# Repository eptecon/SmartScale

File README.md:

SmartScale: Connected Scale for weight measurement
======

WiFi connected scale.

### Hardware

ESP32 Microcontroller, sparkfun's [OpenScale](https://www.sparkfun.com/products/13261).

### Firmware

The firmware consists of RTOS and applications for measuring and analysing of weight data from sparkfun's [OpenScale](https://www.sparkfun.com/products/13261). 
The data from the scale is sent over UART to ESP32. ESP32 is also able to configure the scale. It connects to a cloud service and provides weight data over MQTT.

## Software

Immediately after connecting with a server over WLAN, the device starts to send the measured weights to the cloud service ([GlueLogics](https://github.com/eptecon/gluelogics)) enabling analytics for your working environment, even without invasive notifications.

---

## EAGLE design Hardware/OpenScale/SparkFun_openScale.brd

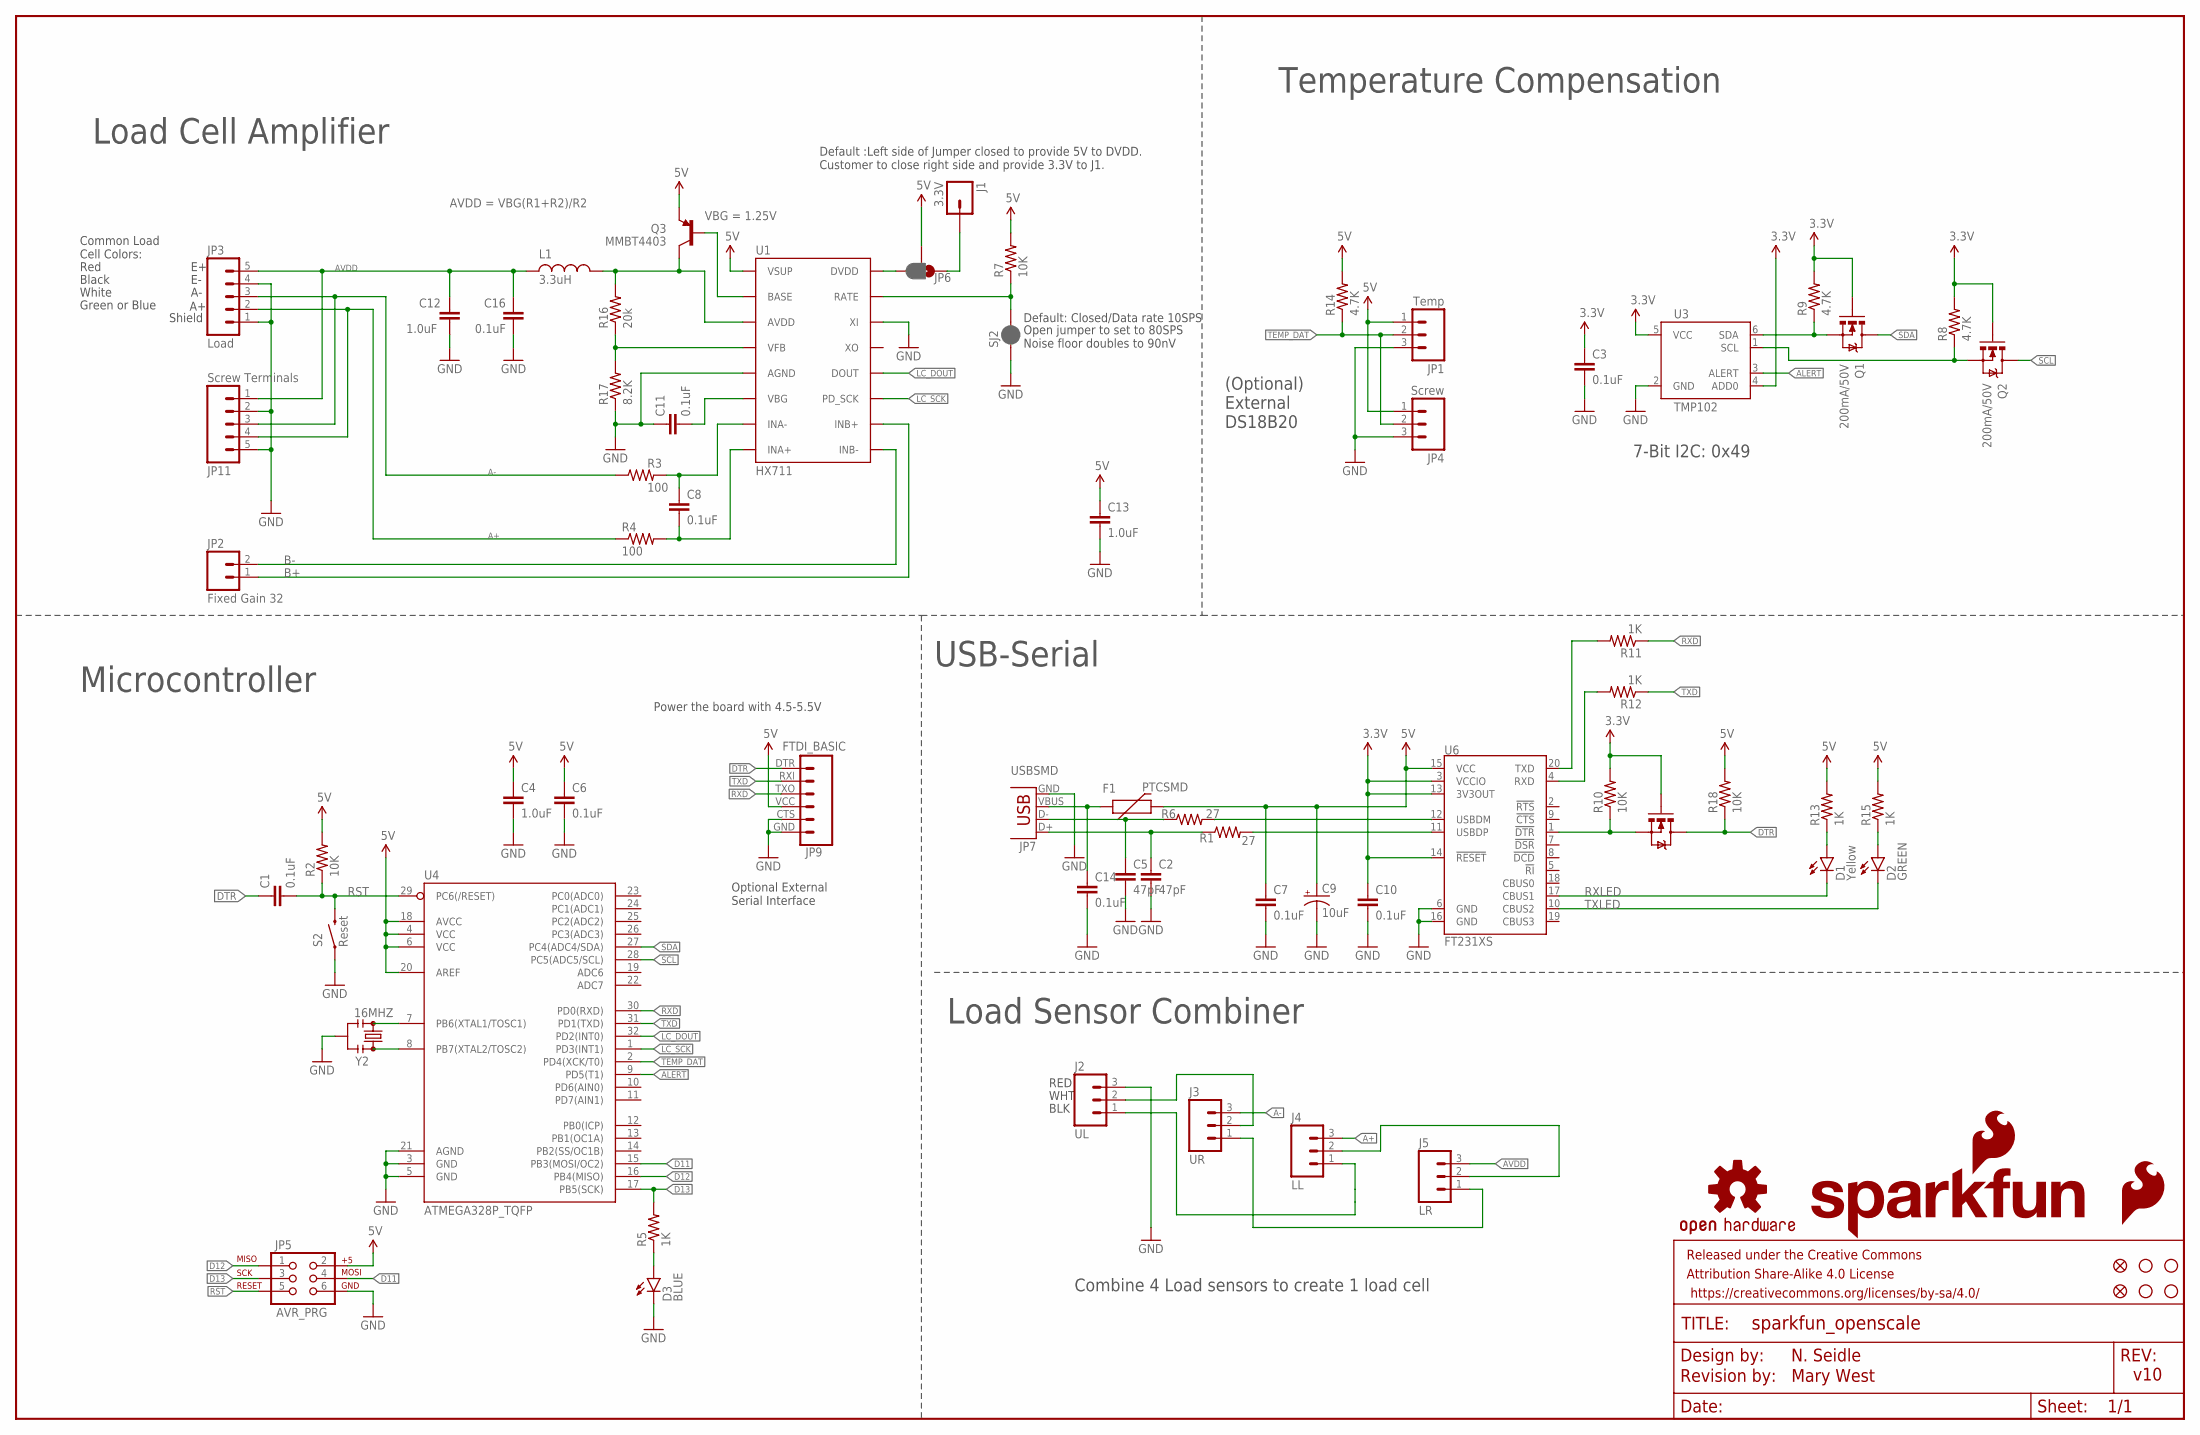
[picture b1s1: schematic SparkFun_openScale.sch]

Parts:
C1, C3, C6, C7, C8, C10, C11, C14, C16: 0.1uF; 0603-CAP
C2, C5: 47pF; 0603-CAP
C4, C12, C13: 1.0uF; 0603-CAP
C9: 10uF; EIA3216
D1: Yellow; LED-1206
D2: GREEN; LED-1206
D3: BLUE; LED-1206
F1: PTCSMD; PTC-1206
FID1, FID2: FIDUCIALUFIDUCIAL; MICRO-FIDUCIAL
FRAME1: FRAME-LEDGER; CREATIVE_COMMONS
J1: 3.3V; 1X01
J2: UL; 1X03
J3: UR; 1X03
J4: LL; 1X03
J5: LR; 1X03
JP1: Temp; 1X03_NO_SILK
JP2: Fixed Gain 32; 1X02
JP3: Load; 1X05_NO_SILK
JP4: Screw; SCREWTERMINAL-3.5MM-3_LOCK.007S
JP5: AVR_PRG; 2X3
JP6: JUMPER-PAD-3-2OF3_NC_BY_PASTE; PAD-JUMPER-3-2OF3_NC_BY_PASTE_YES_SILK_FULL_BOX
JP7: USBSMD; USB-MINIB
JP9: FTDI_BASIC
JP11: Screw Terminals; SCREWTERMINAL-3.5MM-5
L1: 3.3uH; 0805
LOGO2: OSHW-LOGOS; OSHW-LOGO-S
LOGO3: SFE_LOGO_FLAME.1_INCH; SFE_LOGO_FLAME_.1
LOGO4: SFE_LOGO_NAME_FLAME.1_INCH; SFE_LOGO_NAME_FLAME_.1
Q1, Q2: 200mA/50V; SOT23-3
Q3: MMBT4403; SOT23-3
Q4: MOSFET-NCHANNEL2N7002PW; SOT323
R1, R6: 27; 0603
R2, R7, R10, R18: 10K; 0603-RES
R3, R4: 100; 0603-RES
R5, R11, R12, R13, R15: 1K; 0603-RES
R8, R9, R14: 4.7K; 0603-RES
R16: 20k; 0603-RES
R17: 8.2K; 0603-RES
S2: Reset; TACTILE-SWITCH-SMD
SJ2: JUMPER-PAD-2-NC_BY_PASTE; PAD-JUMPER-2-NC_BY_PASTE_YES_SILK
STANDOFF1, STANDOFF2, STANDOFF3, STANDOFF4: STAND-OFF
U1: HX711; SO16
U3: TMP102; SOT563
U4: ATMEGA328P_TQFP; TQFP32-08
U6: FT231XS; SSOP20_L
Y2: 16MHZ; RESONATOR-SMD

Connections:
2: J4.2, J5.2
3.3V: C3.1, C10.1, Q1.1 (G), Q2.1 (G), Q4.1 (G), R8.2, R9.2, R10.2, U3.4 (ADD0), U3.5 (VCC), U6.3 (VCCIO), U6.13 (3V3OUT), U6.14 (!RESET)
5V: C4.1, C6.1, C7.1, C9.A (+), C13.1, F1.2, JP1.1, JP4.1, JP5.2, JP6.2, JP9.VCC (4), Q3.2 (E), R2.2, R7.2, R13.2, R14.2, R15.2, R18.2, U1.1 (VSUP), U4.4 (VCC), U4.6 (VCC), U4.18 (AVCC), U4.20 (AREF), U6.15 (VCC)
A+: J4.3, JP3.2, JP11.4, R4.1
A-: J3.3, JP3.3, JP11.3, R3.1
ALERT: U3.3 (ALERT), U4.9 (PD5(T1))
AVDD: C12.2, C16.1, J5.3, JP3.5, JP11.1, L1.1
B+: JP2.1, U1.10 (INB+)
B-: JP2.2, U1.9 (INB-)
D11: JP5.4, U4.15 (PB3(MOSI/OC2))
D12: JP5.1, U4.16 (PB4(MISO))
D13: JP5.3, R5.2, U4.17 (PB5(SCK))
DTR: C1.1, JP9.DTR (1), Q4.3 (D), R18.1
GND: C2.2, C3.2, C4.2, C5.2, C6.2, C7.2, C9.C (-), C10.2, C11.1, C12.1, C13.2, C14.2, C16.2, D3.C, J2.3, JP1.3, JP3.1, JP3.4, JP4.3, JP5.6, JP7.GND, JP9.CTS (5), JP9.GND (6), JP11.2, JP11.5, R17.1, S2.1, SJ2.1, U1.5 (AGND), U1.14 (XI), U3.2 (GND), U4.3 (GND), U4.5 (GND), U4.21 (AGND), U6.6 (GND), U6.16 (GND), Y2.2
LC_DOUT: U1.12 (DOUT), U4.32 (PD2(INT0))
LC_SCK: U1.11 (PD_SCK), U4.1 (PD3(INT1))
LV_SCL: Q2.2 (S), R8.1, U3.1 (SCL)
LV_SDA: Q1.2 (S), R9.1, U3.6 (SDA)
unnamed: U4.7 (PB6(XTAL1/TOSC1)), Y2.1
unnamed: D3.A, R5.1
unnamed: U4.8 (PB7(XTAL2/TOSC2)), Y2.3
unnamed: C5.1, JP7.D-, R6.1
unnamed: D1.A, R13.1
unnamed: D2.A, R15.1
unnamed: C2.1, JP7.D+, R1.1
unnamed: R6.2, U6.12 (USBDM)
unnamed: R7.1, SJ2.2, U1.15 (RATE)
unnamed: C8.1, R3.2, U1.7 (INA-)
unnamed: C8.2, R4.2, U1.8 (INA+)
unnamed: C14.1, F1.1, JP7.VBUS
unnamed: R1.2, U6.11 (USBDP)
unnamed: R12.2, U6.4 (RXD)
unnamed: JP6.3, U1.16 (DVDD)
unnamed: R11.2, U6.20 (TXD)
unnamed: Q3.1 (B), U1.2 (BASE)
unnamed: R16.1, R17.2, U1.4 (VFB)
unnamed: J1.1, JP6.1
unnamed: J2.2, J3.2
unnamed: C11.2, U1.6 (VBG)
unnamed: J2.1, J4.1
unnamed: J3.1, J5.1
unnamed: Q4.2 (S), R10.1, U6.1 (!DTR)
RIPUP@: L1.2, Q3.3 (C), R16.2, U1.3 (AVDD)
RST: C1.2, JP5.5, R2.1, S2.3 (2), U4.29 (PC6(/RESET))
RXD: JP9.TXO (3), R11.1, U4.30 (PD0(RXD))
RXLED: D1.C, U6.17 (CBUS1)
SCL: Q2.3 (D), U4.28 (PC5(ADC5/SCL))
SDA: Q1.3 (D), U4.27 (PC4(ADC4/SDA))
TEMP_DAT: JP1.2, JP4.2, R14.1, U4.2 (PD4(XCK/T0))
TXD: JP9.RXI (2), R12.1, U4.31 (PD1(TXD))
TXLED: D2.C, U6.10 (CBUS2)

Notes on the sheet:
Microcontroller
USB-Serial
Default: Closed/Data rate 10SPS
Open jumper to set to 80SPS Noise floor doubles to 90nV
Red
Black
White
Green or Blue
Common Load Cell Colors:
Temperature Compensation
(Optional) External DS18B20
Load Cell Amplifier
7-Bit I2C: 0x49
Shield
Optional External Serial Interface
VBG = 1.25V
AVDD = VBG(R1+R2)/R2
v10
N. Seidle
Power the board with 4.5-5.5V
RED
WHT
BLK
Combine 4 Load sensors to create 1 load cell
Load Sensor Combiner
Default :Left side of Jumper closed to provide 5V to DVDD. Customer to close right side and provide 3.3V to J1.
Revision by: Mary West

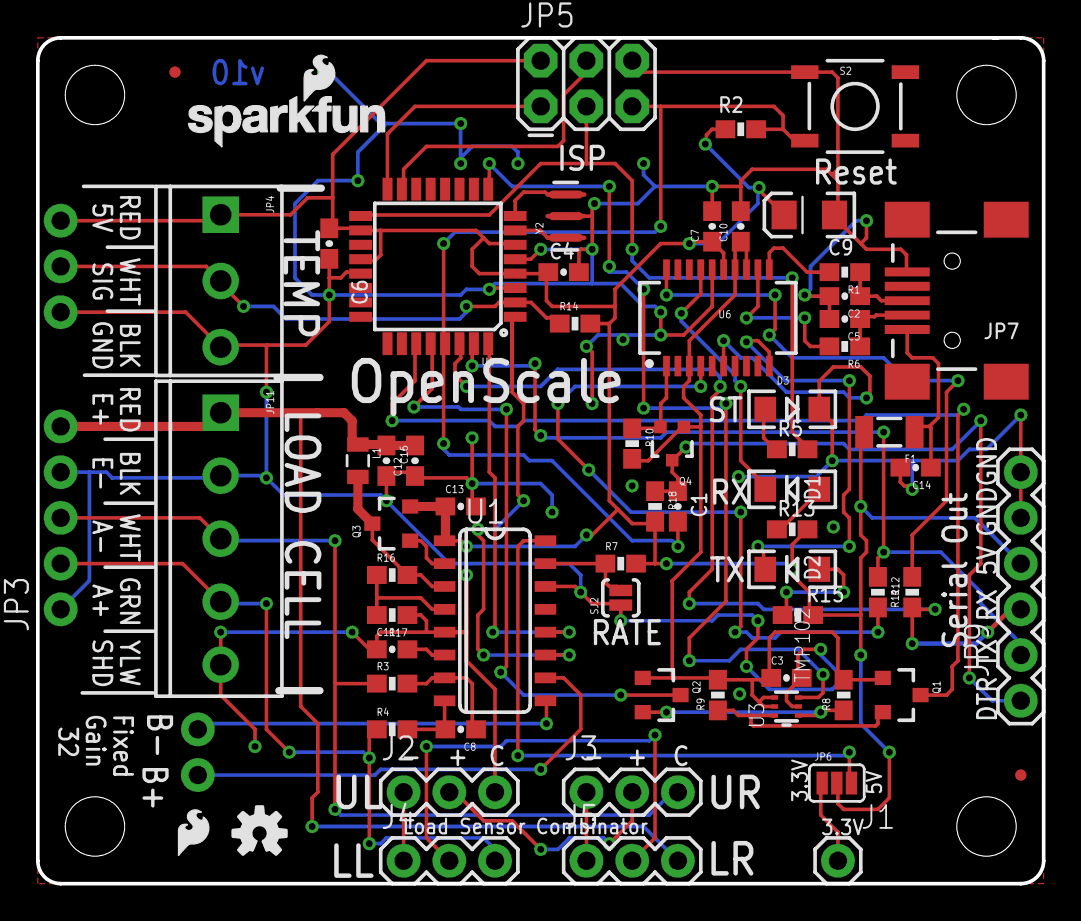
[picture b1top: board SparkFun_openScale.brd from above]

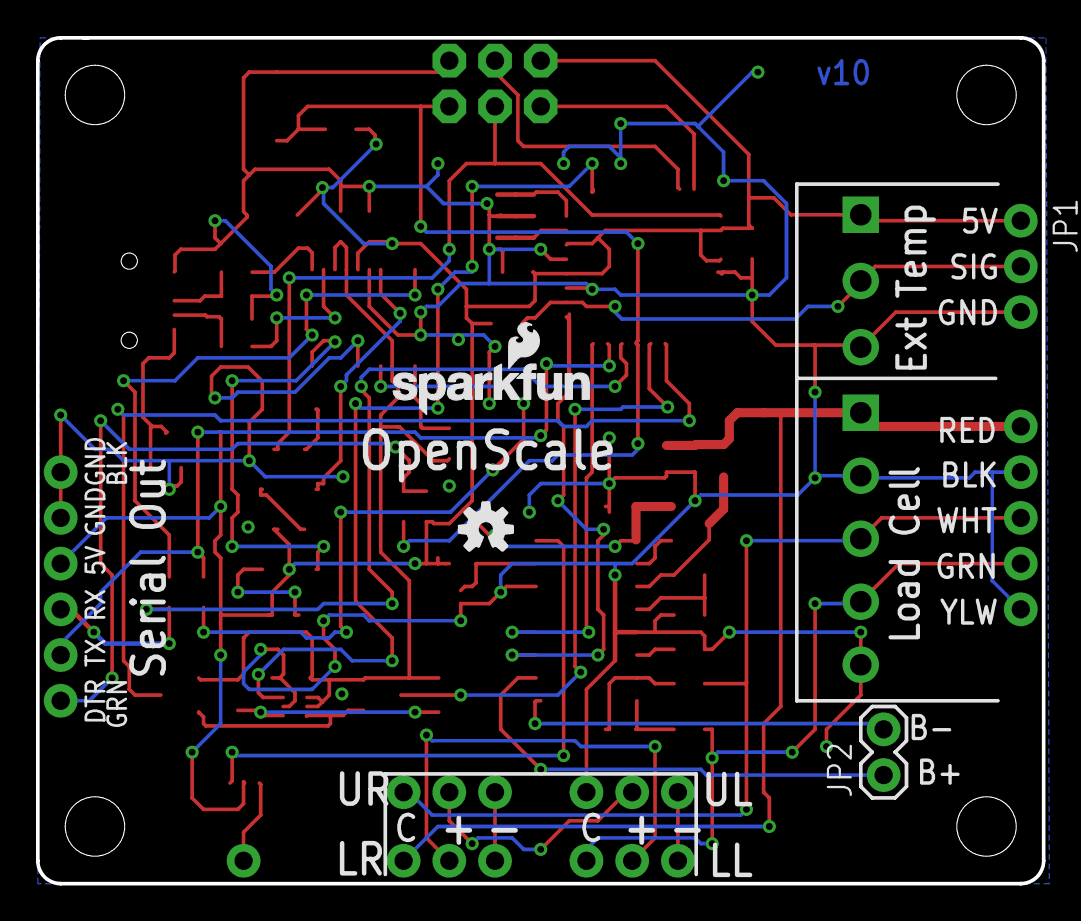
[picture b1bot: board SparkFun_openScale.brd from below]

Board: 2 copper layers, 55.9 x 47.0 mm, 75 parts (4 on the bottom side), 51 nets.

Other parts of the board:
LOGO1: SFE_LOGO_NAME_FLAME.1_INCH; SFE_LOGO_NAME_FLAME_.1
LOGO5: OSHW-LOGOS; OSHW-LOGO-S

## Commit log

2021-05-29 readme update
2021-06-28 license added
2021-09-04 Update LICENSE

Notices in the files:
parts and their libraries:
SparkFun-Aesthetics: Licensing: CC v3.0 Share-Alike You are welcome to use this library for commercial purposes.
SparkFun-Aesthetics: Released under the Creative Commons Attribution Share-Alike 4.0 License
SparkFun-Aesthetics: https://creativecommons.org/licenses/by-sa/4.0
